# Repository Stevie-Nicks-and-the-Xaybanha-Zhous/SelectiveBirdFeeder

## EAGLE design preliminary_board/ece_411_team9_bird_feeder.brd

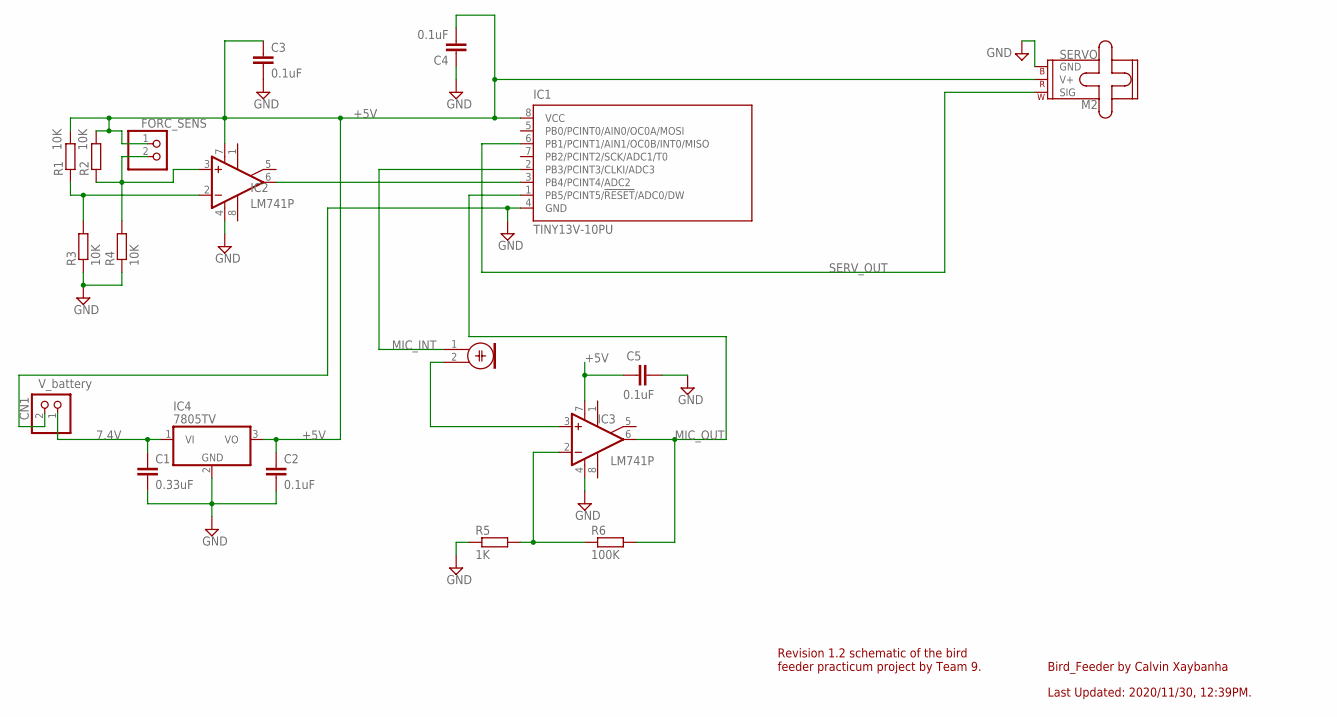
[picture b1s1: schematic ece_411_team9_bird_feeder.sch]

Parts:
C1: 0.33uF; C0805
C2, C3, C4, C5: 0.1uF; C0805
CN1: V_battery; JST-PH-2-SMT
FORC_SENS: PINHD-1X2/90; 1X02/90
IC1: TINY13V-10PU; DIL08
IC2, IC3: LM741P; DIL08
IC4: 7805TV; TO220V
M1: ELECTRET_MICROPHON-WM.64PN; WM-64PN
M2: SERVO; 1X03
R1, R2, R3, R4: 10K; R0805
R5: 1K; R0805
R6: 100K; R0805

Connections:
7.4V: C1.1, CN1.1 (2), IC4.1 (VI)
+5V: C2.1, C3.1, C4.2, C5.1, FORC_SENS.1, IC1.8 (VCC), IC2.7 (V+), IC3.7 (V+), IC4.3 (VO), M2.2 (V+), R1.2, R2.2; also elsewhere on the board
FSNS_OP2: IC2.2 (-IN), R1.1, R3.2
FSNS_OP3: FORC_SENS.2, IC2.3 (+IN), R2.1, R4.2
FSNS_OUT: IC1.3 (PB4/PCINT4/ADC2), IC2.6 (OUT)
GND: C1.2, C2.2, C3.2, C4.1, C5.2, CN1.2 (1), IC1.4 (GND), IC2.4 (V-), IC3.4 (V-), IC4.2 (GND), M2.3 (GND), R3.1, R4.1, R5.1; also elsewhere on the board
MIC_INT: IC1.2 (PB3/PCINT3/CLKI/ADC3), M1.1
MIC_OP2: IC3.2 (-IN), R5.2, R6.1
MIC_OP3: IC3.3 (+IN), M1.2
MIC_OUT: IC1.1 (PB5/PCINT5/!RESET!/ADC0/DW), IC3.6 (OUT), R6.2; also elsewhere on the board
MOSI: IC1.5 (PB0/PCINT0/AIN0/OC0A/MOSI); also elsewhere on the board
SCK: IC1.7 (PB2/PCINT2/SCK/ADC1/T0); also elsewhere on the board
SERV_OUT: IC1.6 (PB1/PCINT1/AIN1/OC0B/INT0/MISO), M2.1 (SIG); also elsewhere on the board

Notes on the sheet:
Bird_Feeder by Calvin Xaybanha
Last Updated: 2020/11/30, 12:39PM.
Revision 1.2 schematic of the bird feeder practicum project by Team 9.

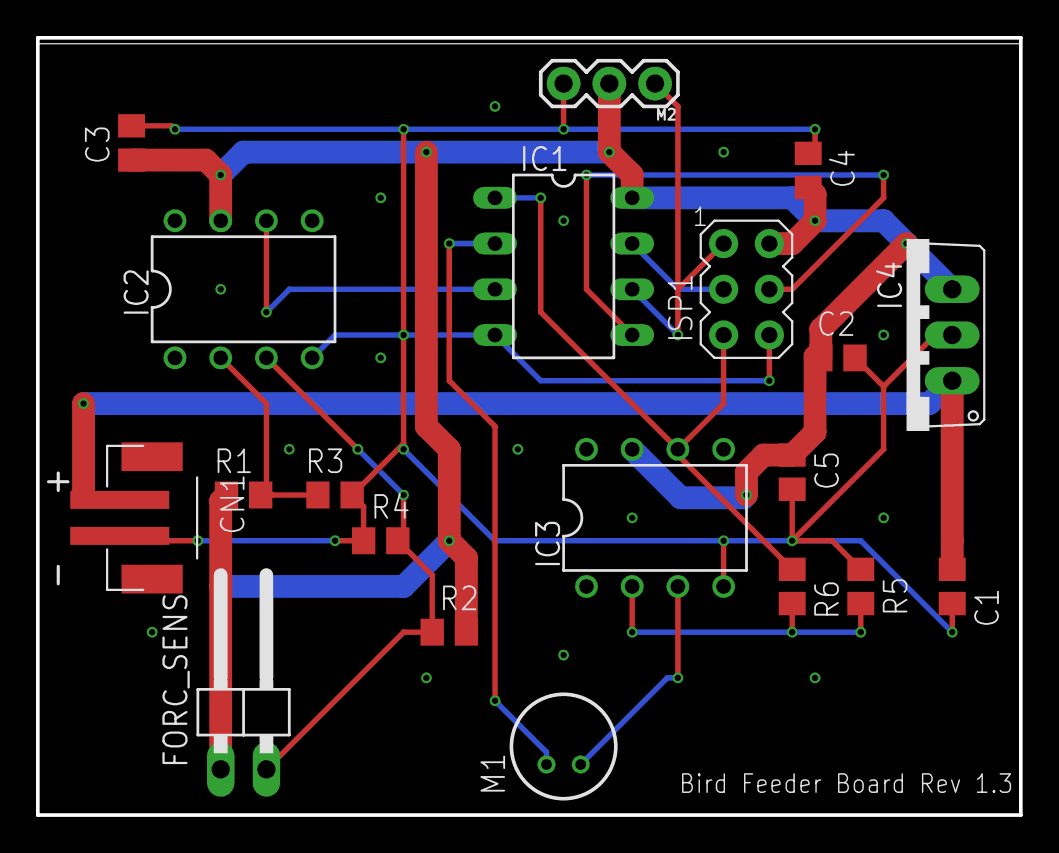
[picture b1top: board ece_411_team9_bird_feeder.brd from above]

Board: 2 copper layers, 54.6 x 43.2 mm, 20 parts (0 on the bottom side), 13 nets.

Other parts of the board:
ISP1: AVRISP-6; AVRISP

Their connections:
+5V: ISP1.2; also elsewhere on the board
GND: ISP1.6; also elsewhere on the board
MIC_OUT: ISP1.5; also elsewhere on the board
MOSI: ISP1.4; also elsewhere on the board
SCK: ISP1.3; also elsewhere on the board
SERV_OUT: ISP1.1; also elsewhere on the board

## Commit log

2020-10-19 Names added to doc
2020-10-23 Add files via upload
    there's also a basin
2020-11-02 Add files via upload
    Picture of the first breadboard prototype. Very unfinished, just put them all together to show we have the parts and are working on the logic of what we're going to do.
2020-11-05 Add files via upload
    Updated the PDS based on our feedback from class on 11/5/2020.
2020-11-29 Add files via upload
    Ver. 1.1 Added stitching vias to ground.
2020-11-30 Delete schematic.pdf
    Old schematic by Nick.
2020-11-30 Delete Smart Bird Feeder.sch
    Old Schematic by Nick.
2020-12-08 Revert "Delete Smart Bird Feeder.sch"
    This reverts commit 9a062cfc9c5c2d0201783edef3fd41efebedd619.
2020-12-08 Revert "Delete schematic.pdf"
    This reverts commit 6cc55b8744200834f0f4132ad1910ad3600d00bc.
2020-12-09 Add files via upload
    Added costs
2020-12-09 Create 3D_CAD_Model
2020-12-09 Organized the schematic,board, and CAD models
    These were put into folders.
2020-12-09 Everything in Folders
    except the powerpoint
2020-12-09 Add files via upload
    Added Calvin's slides. Just need to finish the level 1 block diagram and Nick's code and his state diagram.
2020-12-09 Add files via upload
    Added my level 1 diagram. Just waiting on Nick's code and state diagram now.
2020-12-09 Create TestCase1.jpg
    Creating directory for test cases.
2020-12-09 Add files via upload
    Modified some design slides.
2020-12-09 Add files via upload
    Added comments and removed extraneous code.
2020-12-09 Renamed
2020-12-09 Add files via upload
    Reuploading just in case I changed anything last second.
2020-12-09 Add files via upload
    Forgot to save it after adding the demo links - this is as it was when we presented.

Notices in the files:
parts and their libraries:
SparkFun-Electromechanical: Licensing: Creative Commons ShareAlike 4.0 International - https://creativecommons.org/licenses/by-sa/4.0
